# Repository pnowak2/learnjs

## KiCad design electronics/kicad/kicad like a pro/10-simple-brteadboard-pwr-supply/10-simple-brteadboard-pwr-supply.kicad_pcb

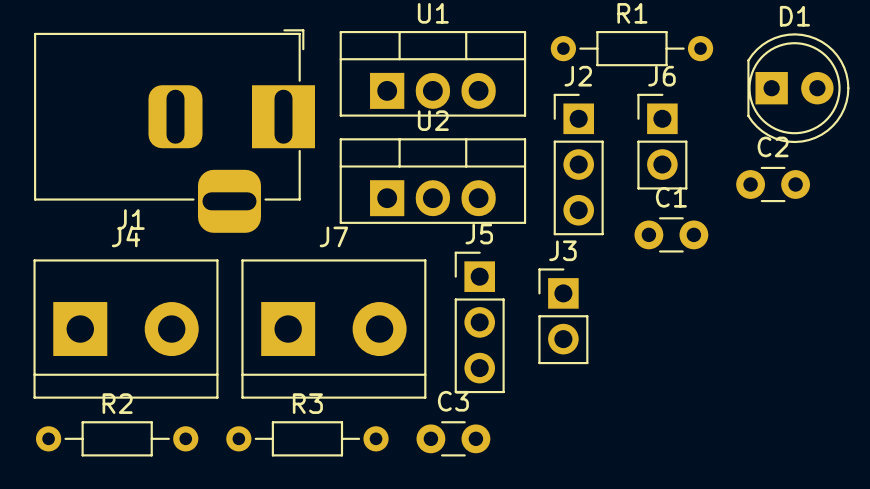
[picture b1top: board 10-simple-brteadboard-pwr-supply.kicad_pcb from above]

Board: 2 copper layers, 16 parts (0 on the bottom side), 7 nets, no tracks yet.

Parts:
C1: 10u; C_Disc_D3.0mm_W1.6mm_P2.50mm
C2: 0.1u; C_Disc_D3.0mm_W1.6mm_P2.50mm
C3: 1u; C_Disc_D3.0mm_W1.6mm_P2.50mm
D1: LED; LED_D5.0mm
J1: Barrel_Jack_Switch; BarrelJack_Horizontal
J2, J5: Conn_01x03_Male; PinHeader_1x03_P2.54mm_Vertical
J3, J6: Conn_01x02_Male; PinHeader_1x02_P2.54mm_Vertical
J4, J7: Screw_Terminal_01x02; TerminalBlock_bornier-2_P5.08mm
R1, R2: 330; R_Axial_DIN0204_L3.6mm_D1.6mm_P7.62mm_Horizontal
R3: 560; R_Axial_DIN0204_L3.6mm_D1.6mm_P7.62mm_Horizontal
U1: LM317_TO-220; TO-220-3_Vertical
U2: LM7805_TO220; TO-220-3_Vertical

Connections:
/3.3V: C3.1, J2.1, J5.1, R2.2, U1.2 (VO)
/5V: C2.1, J2.3, J5.3, U2.3 (VO)
/12V: C1.1, R1.2, U1.3 (VI), U2.1 (VI)
/PWR_output: J2.2, J3.2, J4.2, J5.2, J6.2, J7.2
GND: C1.2, C2.2, C3.2, D1.1 (K), J1.2, J1.3, J3.1, J4.1, J6.1, J7.1, R3.1, U2.2 (GND)
unnamed: D1.2 (A), R1.1
unnamed: R2.1, R3.2, U1.1 (ADJ)

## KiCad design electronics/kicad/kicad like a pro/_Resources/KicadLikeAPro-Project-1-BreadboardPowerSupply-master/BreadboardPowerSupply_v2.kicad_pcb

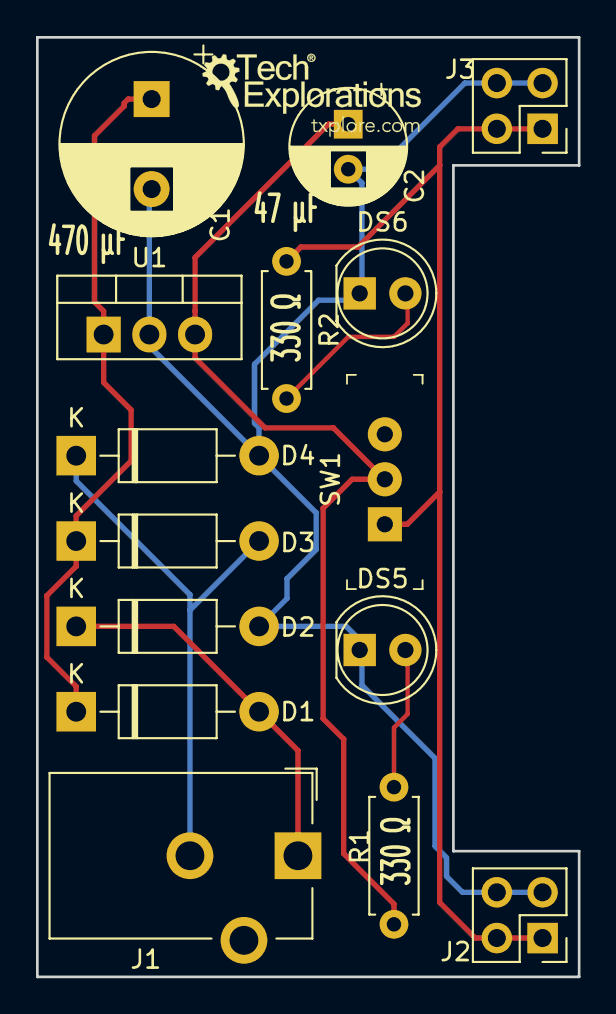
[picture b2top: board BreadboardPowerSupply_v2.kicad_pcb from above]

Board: 2 copper layers, 30.1 x 52.2 mm, 15 parts (0 on the bottom side), 8 nets.

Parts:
C1: CP; CP_Radial_D10.0mm_P5.00mm
C2: CP; CP_Radial_D6.3mm_P2.50mm
D1, D2, D3, D4: D; D_DO-41_SOD81_P10.16mm_Horizontal
DS5, DS6: LED; LED_D5.0mm
J1: Barrel_Jack_Switch; BarrelJack_CUI_PJ-102AH_Horizontal
J2, J3: Conn_02x02_Odd_Even; PinHeader_2x02_P2.54mm_Vertical
R1, R2: R; R_Axial_DIN0207_L6.3mm_D2.5mm_P7.62mm_Horizontal
SW1: SW_DPDT_x2; Switch_Slide_11.6x4mm_EG1218
U1: LM7805_TO220; TO-220-3_Vertical

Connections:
/V1: D1.2, D2.1, J1.1
/V2: D3.2, D4.1, J1.2
/V-: C1.2, C2.2, D2.2, D4.2, DS5.1, DS6.1, J2.3, J2.4, J3.3, J3.4, U1.2
/Vin: C1.1, D1.1, D3.1, U1.1
/Vout1: C2.1, R1.1, SW1.2, U1.3
/Vout2: J2.1, J2.2, J3.1, J3.2, R2.1, SW1.1
unnamed: DS5.2, R1.2
unnamed: DS6.2, R2.2

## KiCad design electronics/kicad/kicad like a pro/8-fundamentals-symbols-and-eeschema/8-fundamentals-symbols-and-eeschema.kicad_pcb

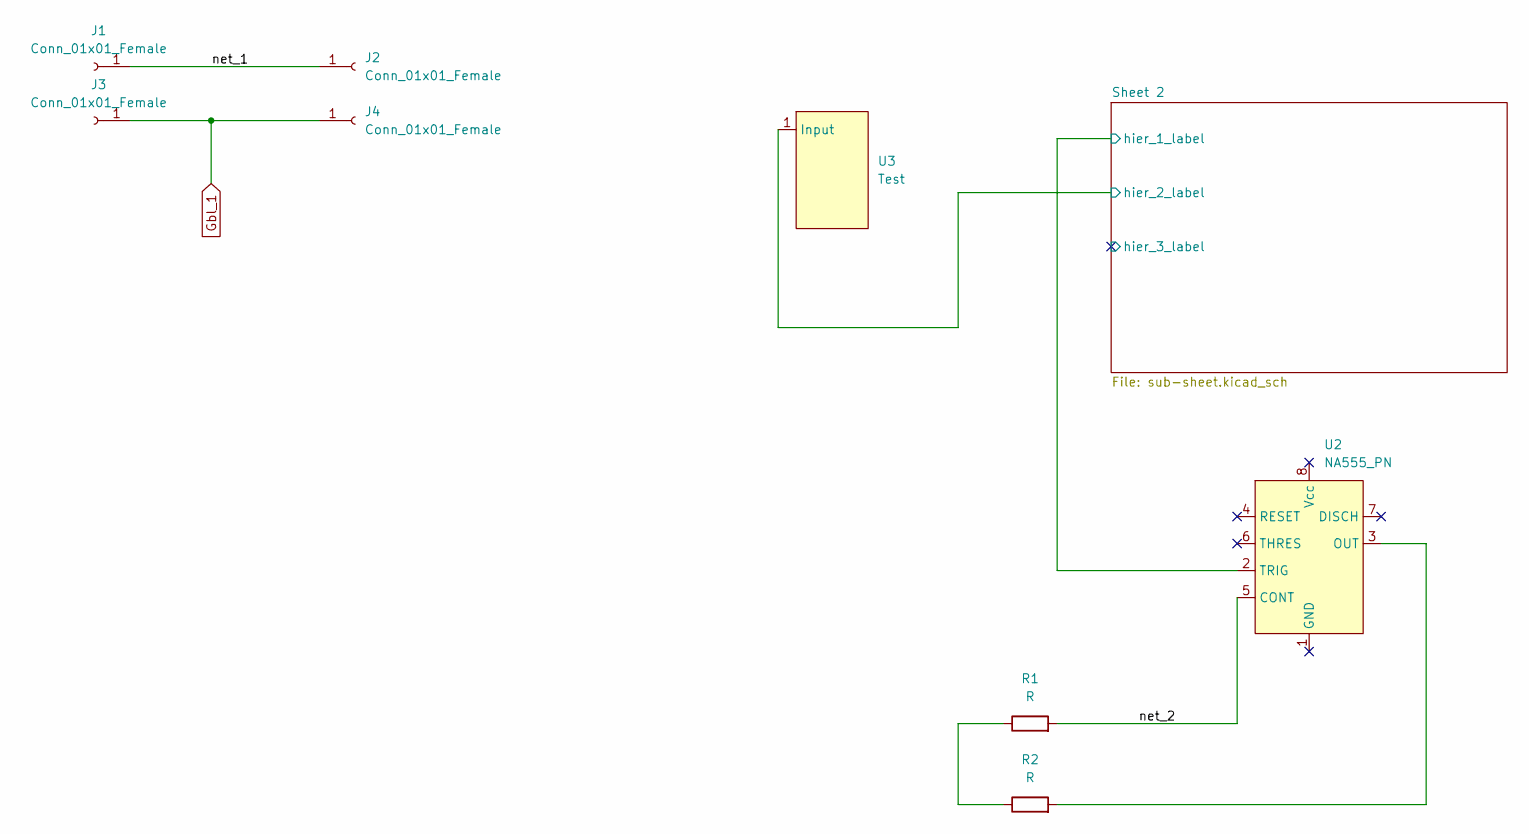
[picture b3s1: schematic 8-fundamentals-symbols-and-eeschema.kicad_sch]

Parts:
J1, J2, J3, J4: Conn_01x01_Female; Pin_D0.7mm_L6.5mm_W1.8mm_FlatFork
R1: R; R_Axial_DIN0207_L6.3mm_D2.5mm_P7.62mm_Horizontal
R2: R; R_0603_1608Metric_Pad0.98x0.95mm_HandSolder
U2: NA555_PN; DIP-8_W7.62mm
U3: Test; CP_Elec_3x5.4

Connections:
/Sheet 2/hier_1_label: U2.2 (TRIG); also elsewhere on the board
/Sheet 2/hier_2_label: U3.1 (Input); also elsewhere on the board
/net_1: J1.1, J2.1
/net_2: R1.2, U2.5 (CONT)
Global_1: J3.1, J4.1; also elsewhere on the board
unnamed: R1.1, R2.1
unnamed: R2.2, U2.3 (OUT)

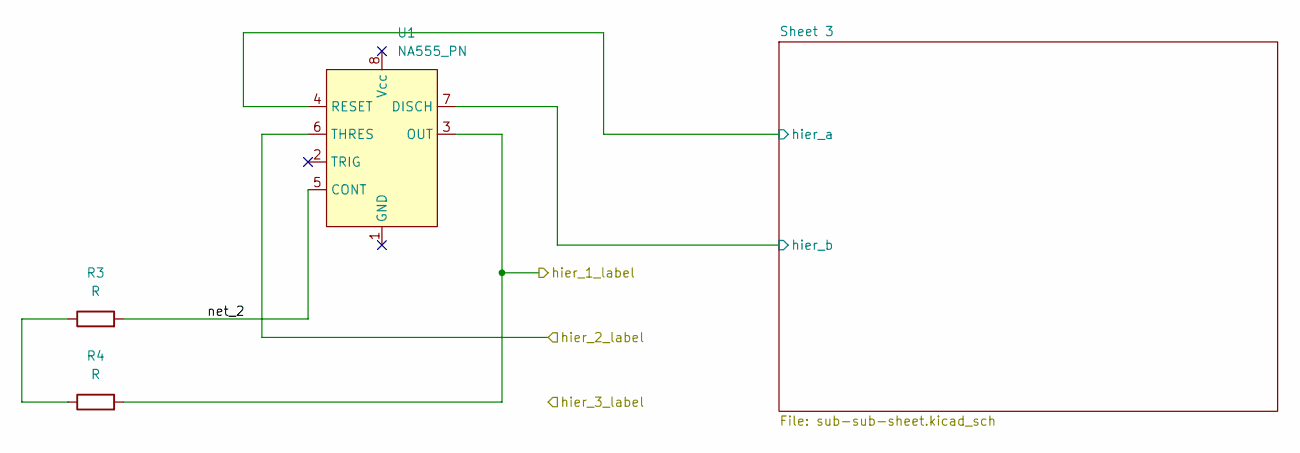
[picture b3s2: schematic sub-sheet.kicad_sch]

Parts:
R3: R; R_Axial_DIN0207_L6.3mm_D2.5mm_P7.62mm_Horizontal
R4: R; R_0603_1608Metric_Pad0.98x0.95mm_HandSolder
U1: NA555_PN; DIP-8_W7.62mm

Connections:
/Sheet 2/Sheet 3/hier_a: U1.4 (RESET); also elsewhere on the board
/Sheet 2/Sheet 3/hier_b: U1.7 (DISCH); also elsewhere on the board
/Sheet 2/hier_1_label: R4.2, U1.3 (OUT); also elsewhere on the board
/Sheet 2/hier_2_label: U1.6 (THRES); also elsewhere on the board
/Sheet 2/net_2: R3.2, U1.5 (CONT)
unnamed: R3.1, R4.1

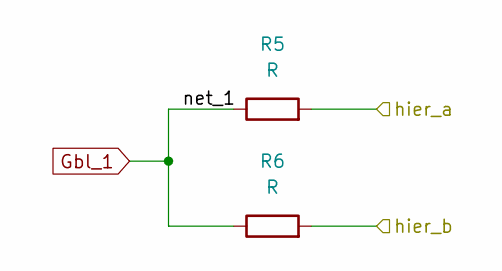
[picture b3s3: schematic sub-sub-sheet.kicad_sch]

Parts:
R5: R; R_Axial_DIN0207_L6.3mm_D2.5mm_P7.62mm_Horizontal
R6: R; R_0603_1608Metric_Pad0.98x0.95mm_HandSolder

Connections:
/Sheet 2/Sheet 3/hier_a: R5.2; also elsewhere on the board
/Sheet 2/Sheet 3/hier_b: R6.2; also elsewhere on the board
Global_1: R5.1, R6.1; also elsewhere on the board

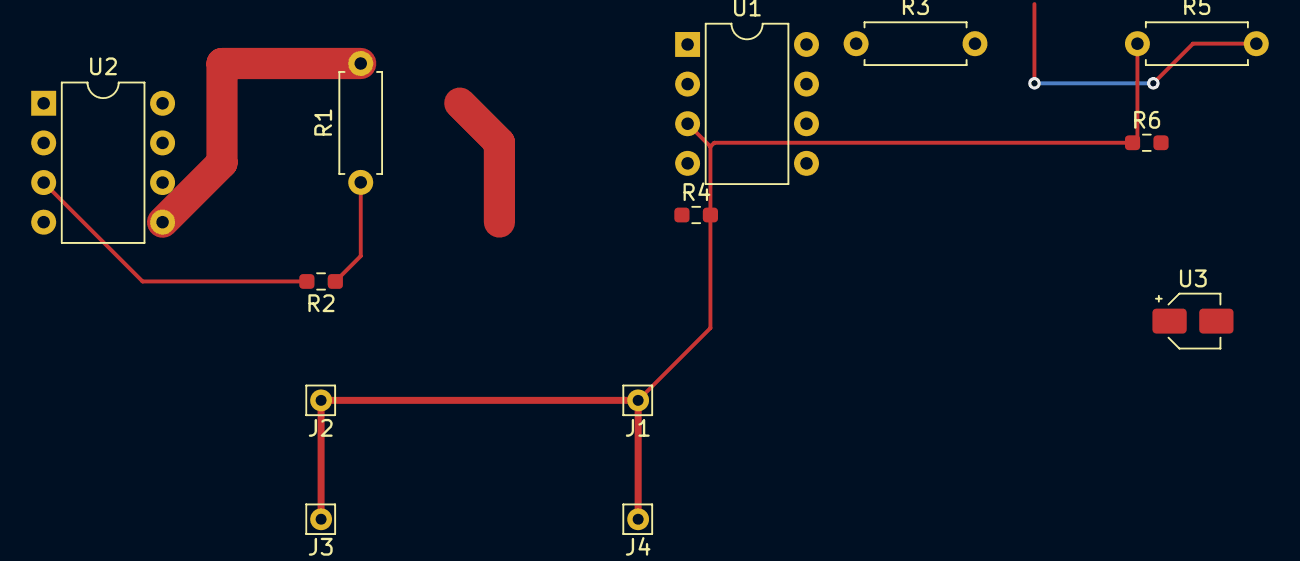
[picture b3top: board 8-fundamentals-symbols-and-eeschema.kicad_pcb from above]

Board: 2 copper layers, 13 parts (0 on the bottom side), 11 nets.

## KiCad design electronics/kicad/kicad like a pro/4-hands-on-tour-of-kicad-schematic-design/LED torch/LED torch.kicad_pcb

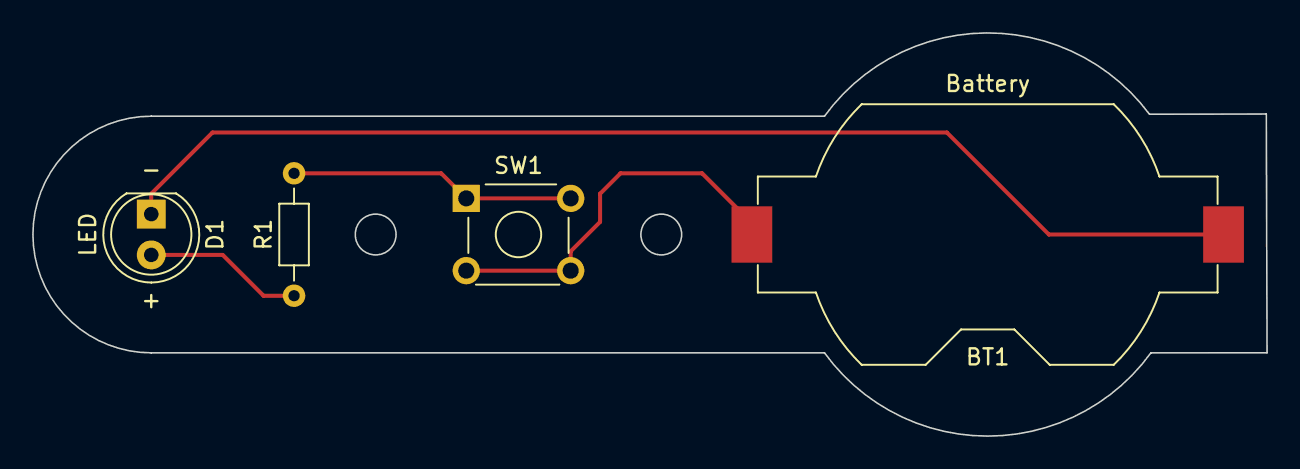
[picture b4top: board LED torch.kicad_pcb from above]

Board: 2 copper layers, 76.8 x 25.1 mm, 4 parts (0 on the bottom side), 4 nets.

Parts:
BT1: Battery; BatteryHolder_Keystone_1058_1x2032
D1: LED; LED_D5.0mm
R1: R; R_Axial_DIN0204_L3.6mm_D1.6mm_P7.62mm_Horizontal
SW1: SW_DPST_x2; SW_TH_Tactile_Omron_B3F-10xx

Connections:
/LED_anode: D1.2 (A), R1.1
/LED_cathode: BT1.2 (-), D1.1 (K)
/bat_pos: BT1.1 (+), SW1.2 (B)
unnamed: R1.2, SW1.1 (A)

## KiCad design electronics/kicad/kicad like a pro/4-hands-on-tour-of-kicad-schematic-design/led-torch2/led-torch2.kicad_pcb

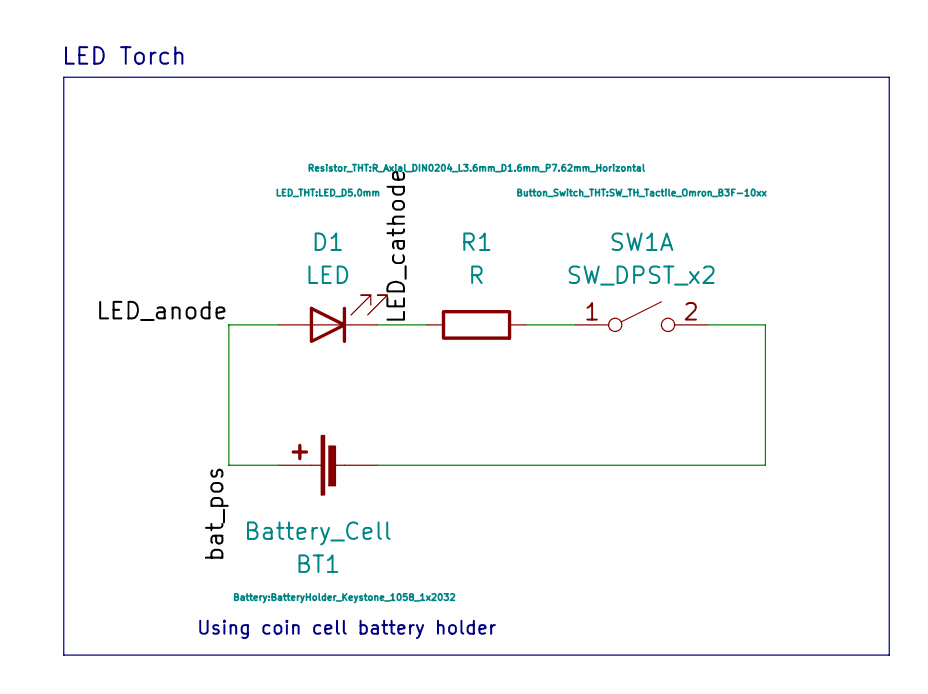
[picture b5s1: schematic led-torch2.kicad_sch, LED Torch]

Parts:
BT1: Battery_Cell; BatteryHolder_Keystone_1058_1x2032
D1: LED; LED_D5.0mm
R1: R; R_Axial_DIN0204_L3.6mm_D1.6mm_P7.62mm_Horizontal
SW1: SW_DPST_x2; SW_TH_Tactile_Omron_B3F-10xx

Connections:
/LED_cathode: D1.1 (K), R1.1
/bat_pos: BT1.1 (+), D1.2 (A)
unnamed: BT1.2 (-), SW1.2 (B)
unnamed: R1.2, SW1.1 (A)

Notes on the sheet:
LED Torch
Using coin cell battery holder

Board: 2 copper layers, 4 parts (0 on the bottom side), 4 nets, no tracks yet.

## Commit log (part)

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2025-09-15 done
2025-10-23 donwe
